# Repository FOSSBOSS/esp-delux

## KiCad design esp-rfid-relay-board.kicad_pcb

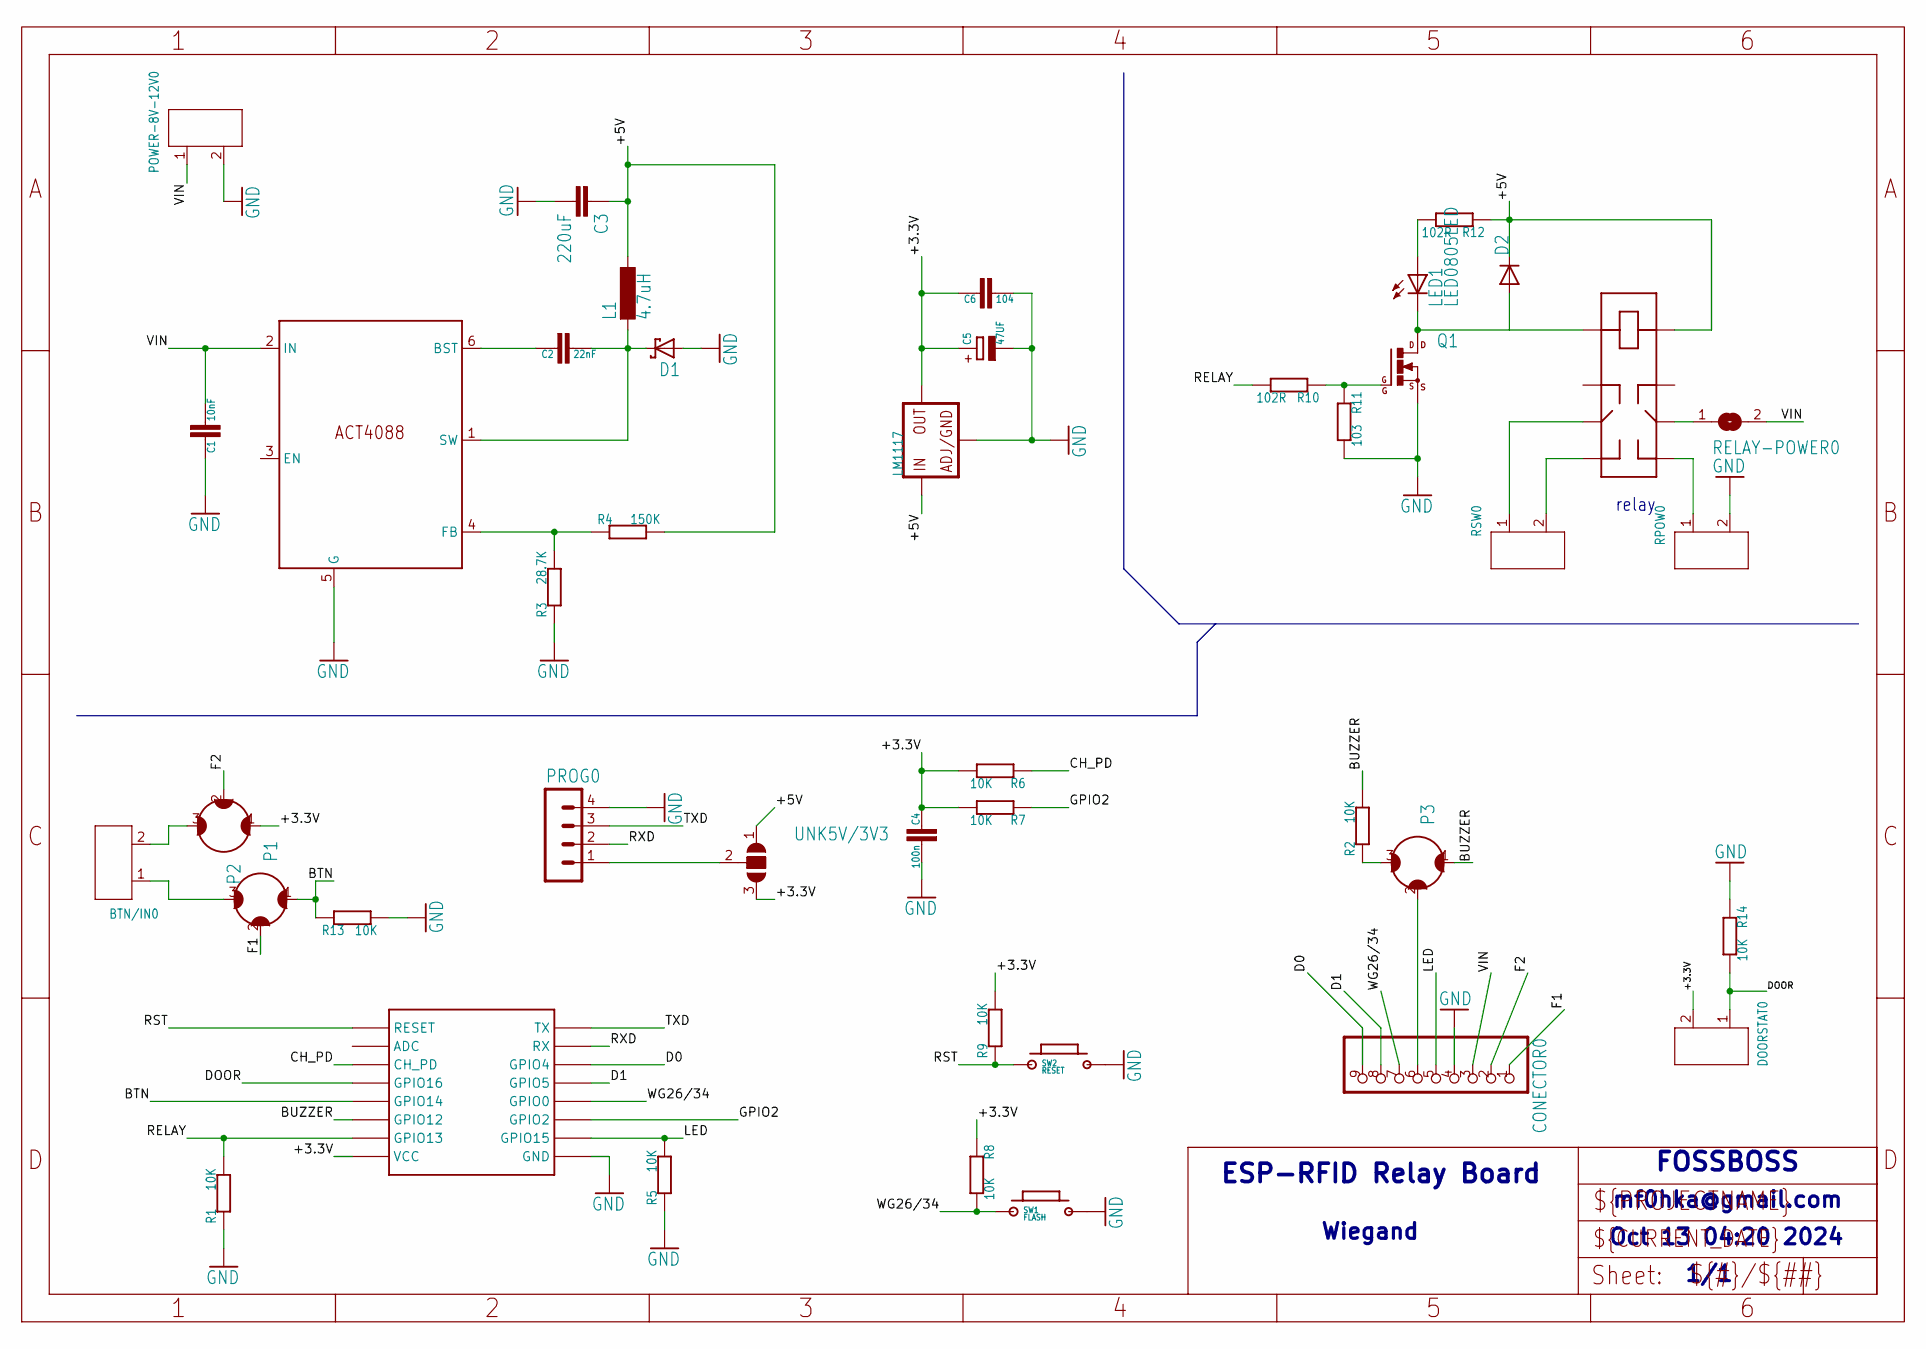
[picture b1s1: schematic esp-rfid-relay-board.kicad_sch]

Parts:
ACT4088: ACT4088; SOT-23-6
BTN/IN0: SCREW-TERMINAL-GREEN(2P-3.5); H2-3.5-7.0X7.0MM
C1: 10nF; C_0805
C2: 22nF; C_0805
C3: 220uF; C1210
C4: 100n; C_0805
C5: 47UF; CPOL_B3528
C6: 104; C_0805
CONECTOR0: PINHD-1X9; 1X09
D1: SCHOTTKY-DIODESMD; SMB
D2: 4007-4148; DIO_SOD123FL
DOORSTAT0: SCREW-TERMINAL-GREEN(2P-3.5); H2-3.5-7.0X7.0MM
L1: 4.7uH; L3225M
LED1: LED0805LED; 0805LED
LM1117: POWERSOT223; SOT223
P1, P2, P3: SJ3; SJ_3
POWER-8V-12V0: SCREW-TERMINAL-GREEN(2P-3.5); H2-3.5-7.0X7.0MM
PROG0: MA04-1
Q1: MOSFET_NSOT23; SOT23
R1, R2, R5, R6, R7, R8, R9, R13, R14: 10K; R_0805
R3: 28.7K; R_0805
R4: 150K; R_0805
R10, R12: 102R; R_0805
R11: 103; R_0805
RELAY0: 2XSWITCH; HFD3-SIGNAL
RELAY-POWER0: SJ
RPOW0: SCREW-TERMINAL-GREEN(2P-3.5); H2-3.5-7.0X7.0MM
RSW0: SCREW-TERMINAL-GREEN(2P-3.5); H2-3.5-7.0X7.0MM
SW1: FLASH; 2P-SWITCH-TURTLE
SW2: RESET; 2P-SWITCH-TURTLE
U2: ESP12SMD; ESP12-SMD
UNK5V/3V3: SJ2W; SJ_2

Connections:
+3.3V: C4.1, C5.+, C6.1, DOORSTAT0.2, LM1117.OUT1 (OUT), LM1117.OUT2 (OUT), P2.1, R6.2, R7.2, R8.1, R9.2, U2.VCC, UNK5V/3V3.3
+5V: C3.1, D2.C, L1.1, LM1117.IN+ (IN), R4.2, R12.1, RELAY0.8, UNK5V/3V3.1
BTN: P1.1, R13.1, U2.GPIO14
BUCK1: ACT4088.1 (SW), C2.2, D1.C, L1.2
BUCK2: ACT4088.4 (FB), R3.2, R4.1
BUCK3: ACT4088.6 (BST), C2.1
BUZZER: P3.1, R2.2, U2.GPIO12
CH_PD: R6.1, U2.CH_PD
D0: CONECTOR0.9, U2.GPIO4
D1: CONECTOR0.8, U2.GPIO5
DOOR: DOORSTAT0.1, R14.2, U2.GPIO16
F1: CONECTOR0.1, P1.2
F2: CONECTOR0.2, P2.2
GND: ACT4088.5 (G), C1.1, C3.2, C4.2, C5.-, C6.2, CONECTOR0.4, D1.A, LM1117.GND, POWER-8V-12V0.2, PROG0.4, Q1.2 (S), R1.1, R3.1, R5.1, R11.2, R13.2, R14.1, RPOW0.2, SW1.2, SW2.2, U2.GND
GPIO2: R7.1, U2.GPIO2
LED: CONECTOR0.5, R5.2, U2.GPIO15
unnamed: PROG0.1, UNK5V/3V3.2
unnamed: RELAY0.6, RELAY-POWER0.1
unnamed: RELAY0.5, RPOW0.1
unnamed: RELAY0.4, RSW0.2
unnamed: BTN/IN0.1, P1.3
unnamed: BTN/IN0.2, P2.3
unnamed: RELAY0.3, RSW0.1
unnamed: CONECTOR0.6, P3.2
unnamed: P3.3, R2.1
RELAY: R1.2, R10.2, U2.GPIO13
RELN1: Q1.1 (G), R10.1, R11.1
RELN2: D2.A, LED1.C, Q1.3 (D), RELAY0.1
RELN4: LED1.A, R12.2
RST: R9.1, SW2.1, U2.RESET
RXD: PROG0.2, U2.RXD0 (RX)
TXD: PROG0.3, U2.TXD0 (TX)
VIN: ACT4088.2 (IN), C1.2, CONECTOR0.3, POWER-8V-12V0.1, RELAY-POWER0.2
WG26/34: CONECTOR0.7, R8.2, SW1.1, U2.GPIO0

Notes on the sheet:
relay
mf0hka@gmail.com
1/1
Wiegand
ESP-RFID Relay Board
Oct 13 04:20 2024
FOSSBOSS

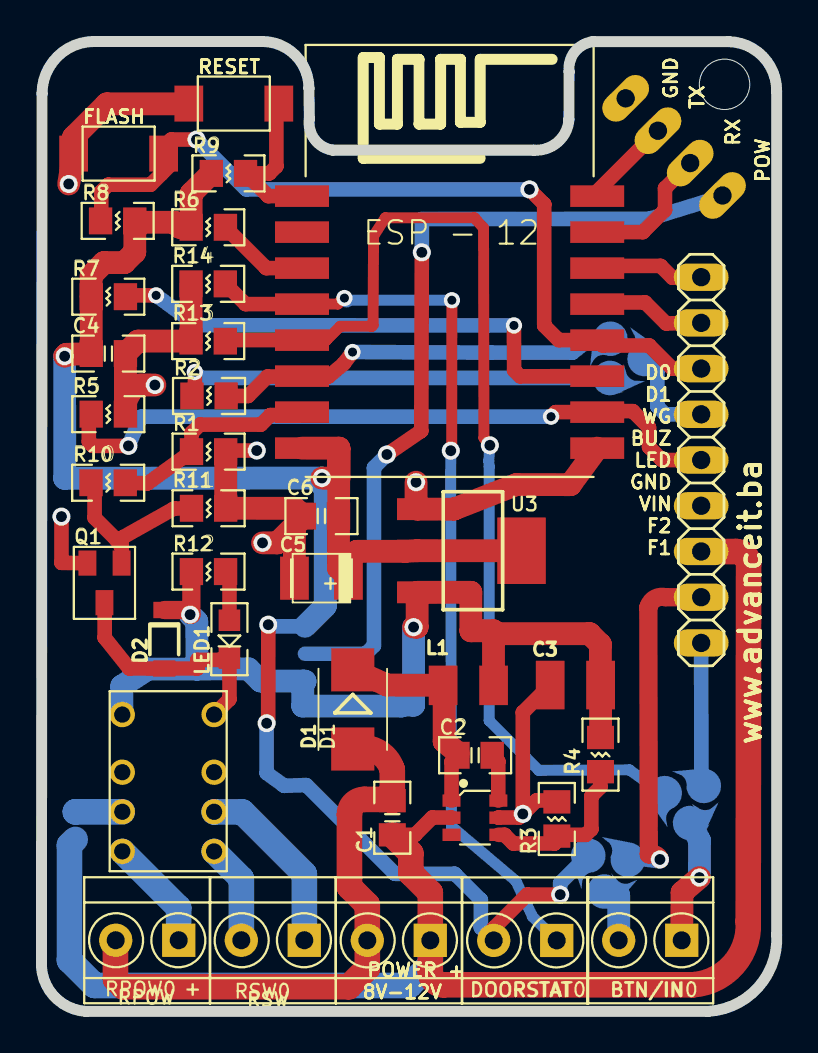
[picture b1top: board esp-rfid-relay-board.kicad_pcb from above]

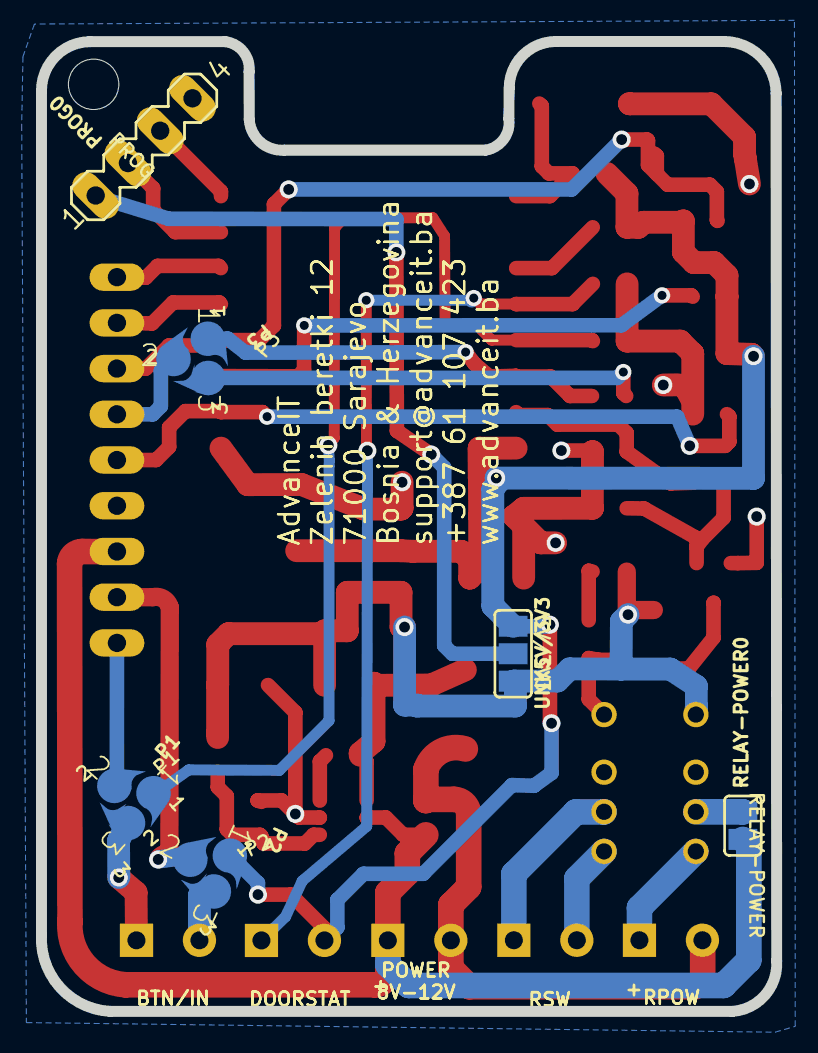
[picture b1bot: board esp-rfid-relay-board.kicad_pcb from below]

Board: 2 copper layers, 40.8 x 53.9 mm, 44 parts (6 on the bottom side), 34 nets.

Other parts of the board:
@HOLE0: (no value)
